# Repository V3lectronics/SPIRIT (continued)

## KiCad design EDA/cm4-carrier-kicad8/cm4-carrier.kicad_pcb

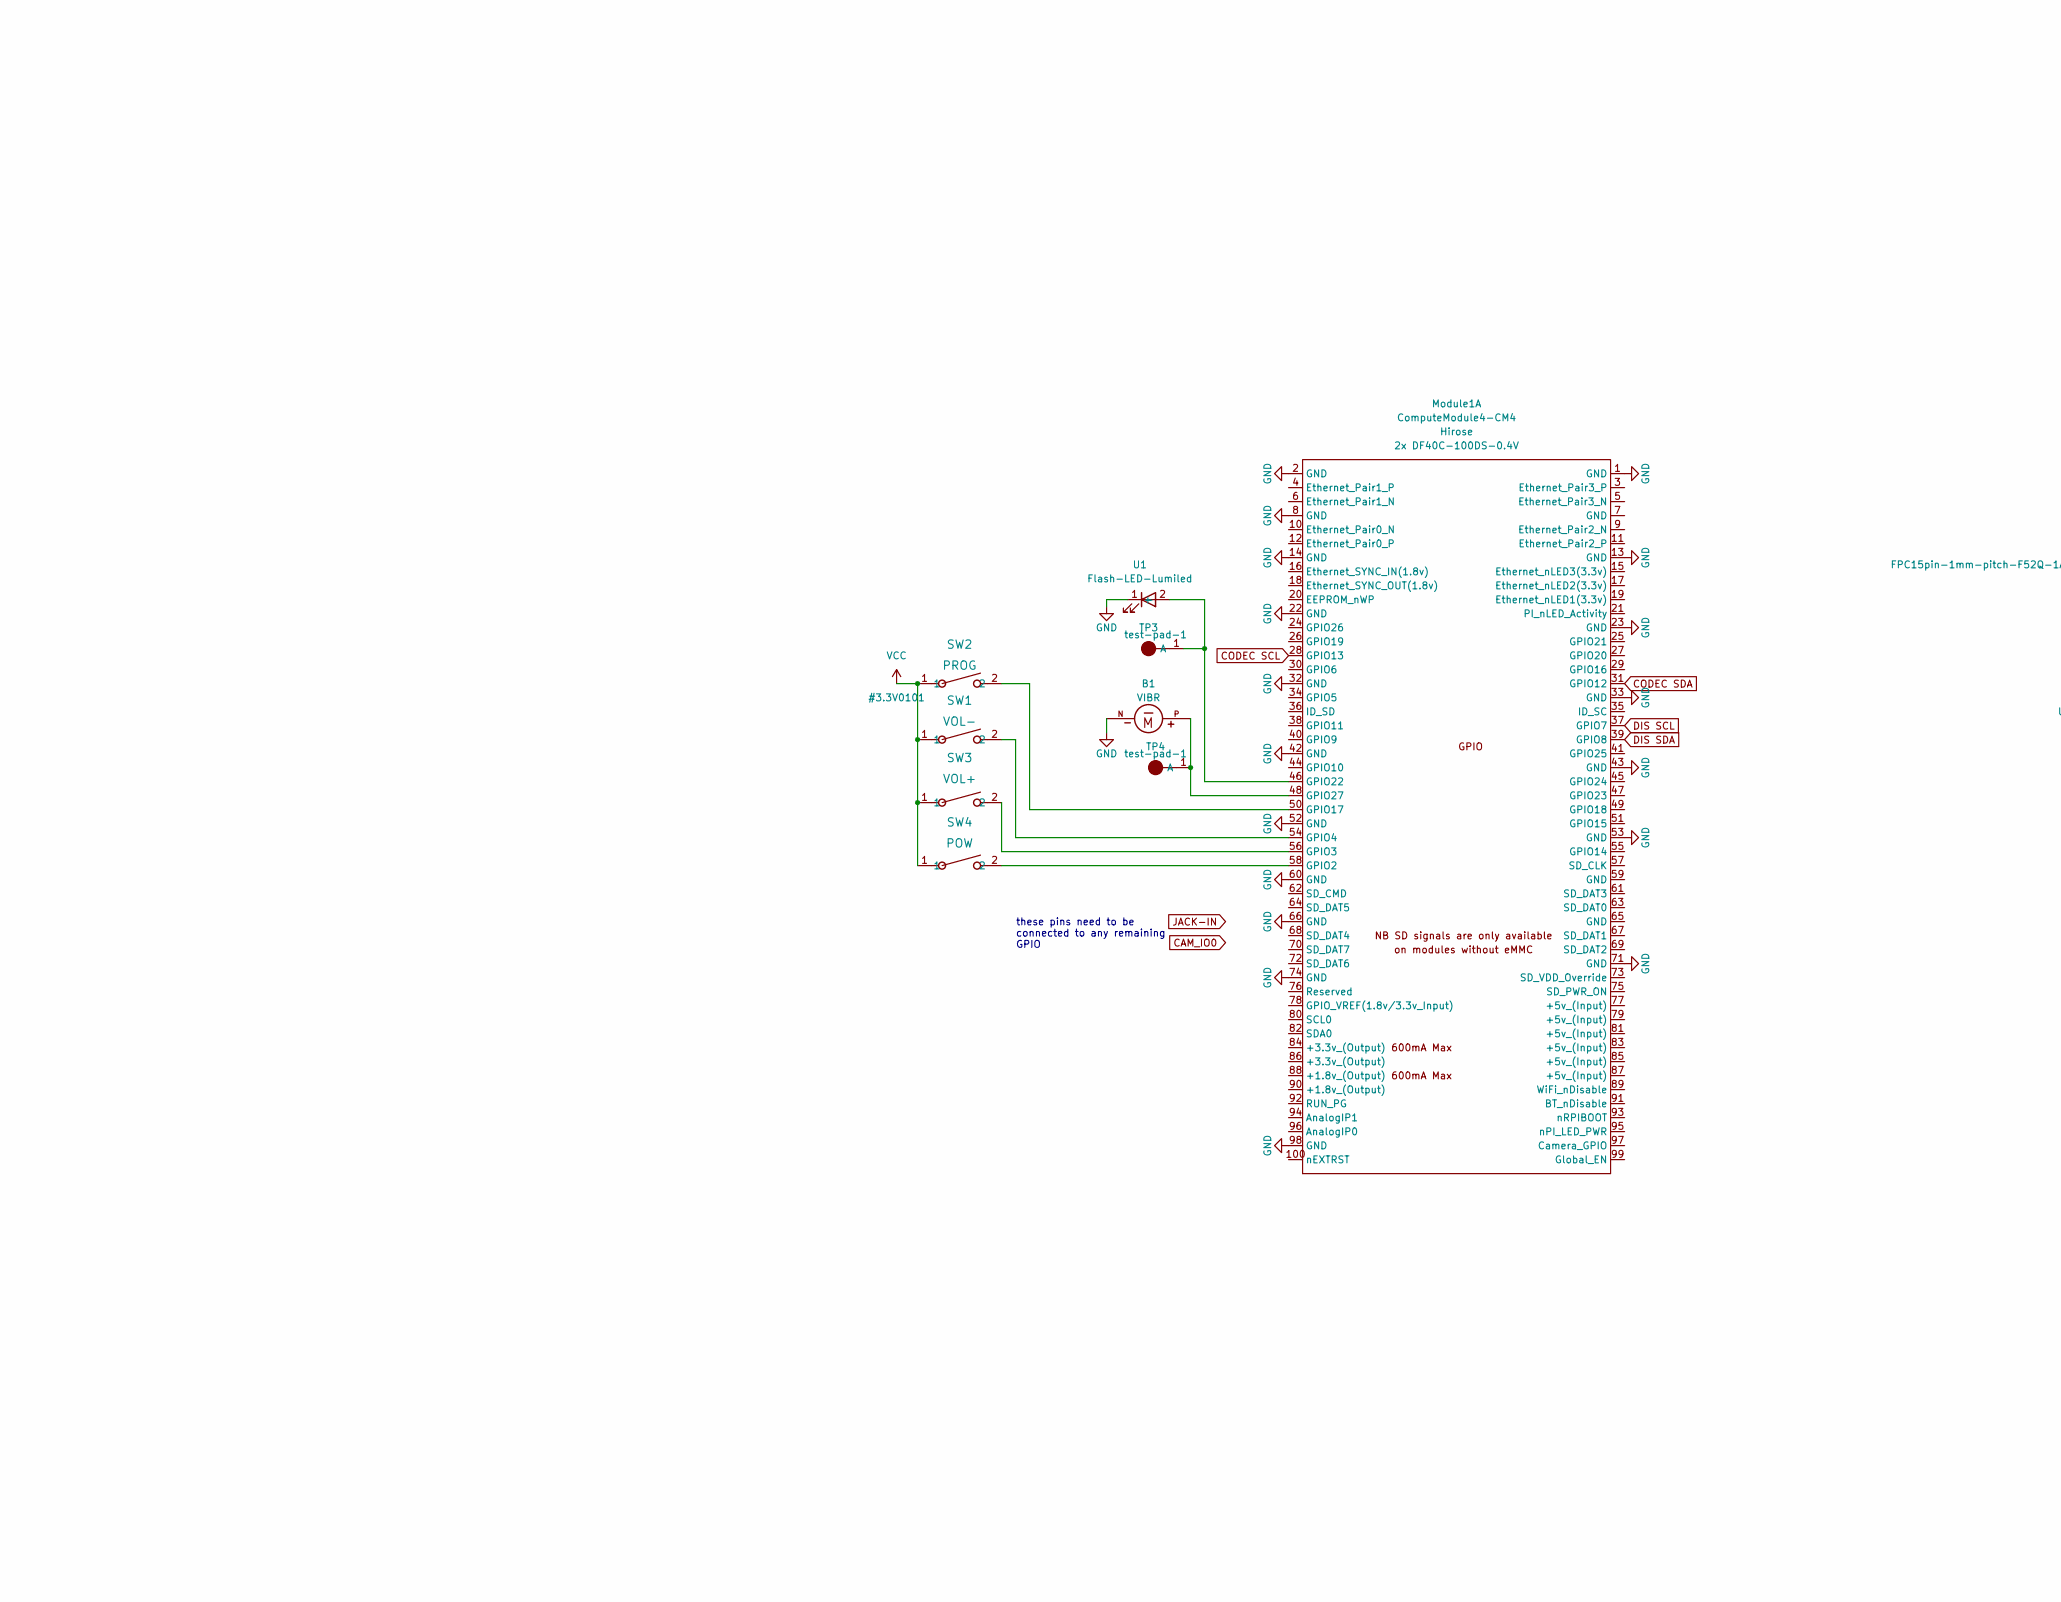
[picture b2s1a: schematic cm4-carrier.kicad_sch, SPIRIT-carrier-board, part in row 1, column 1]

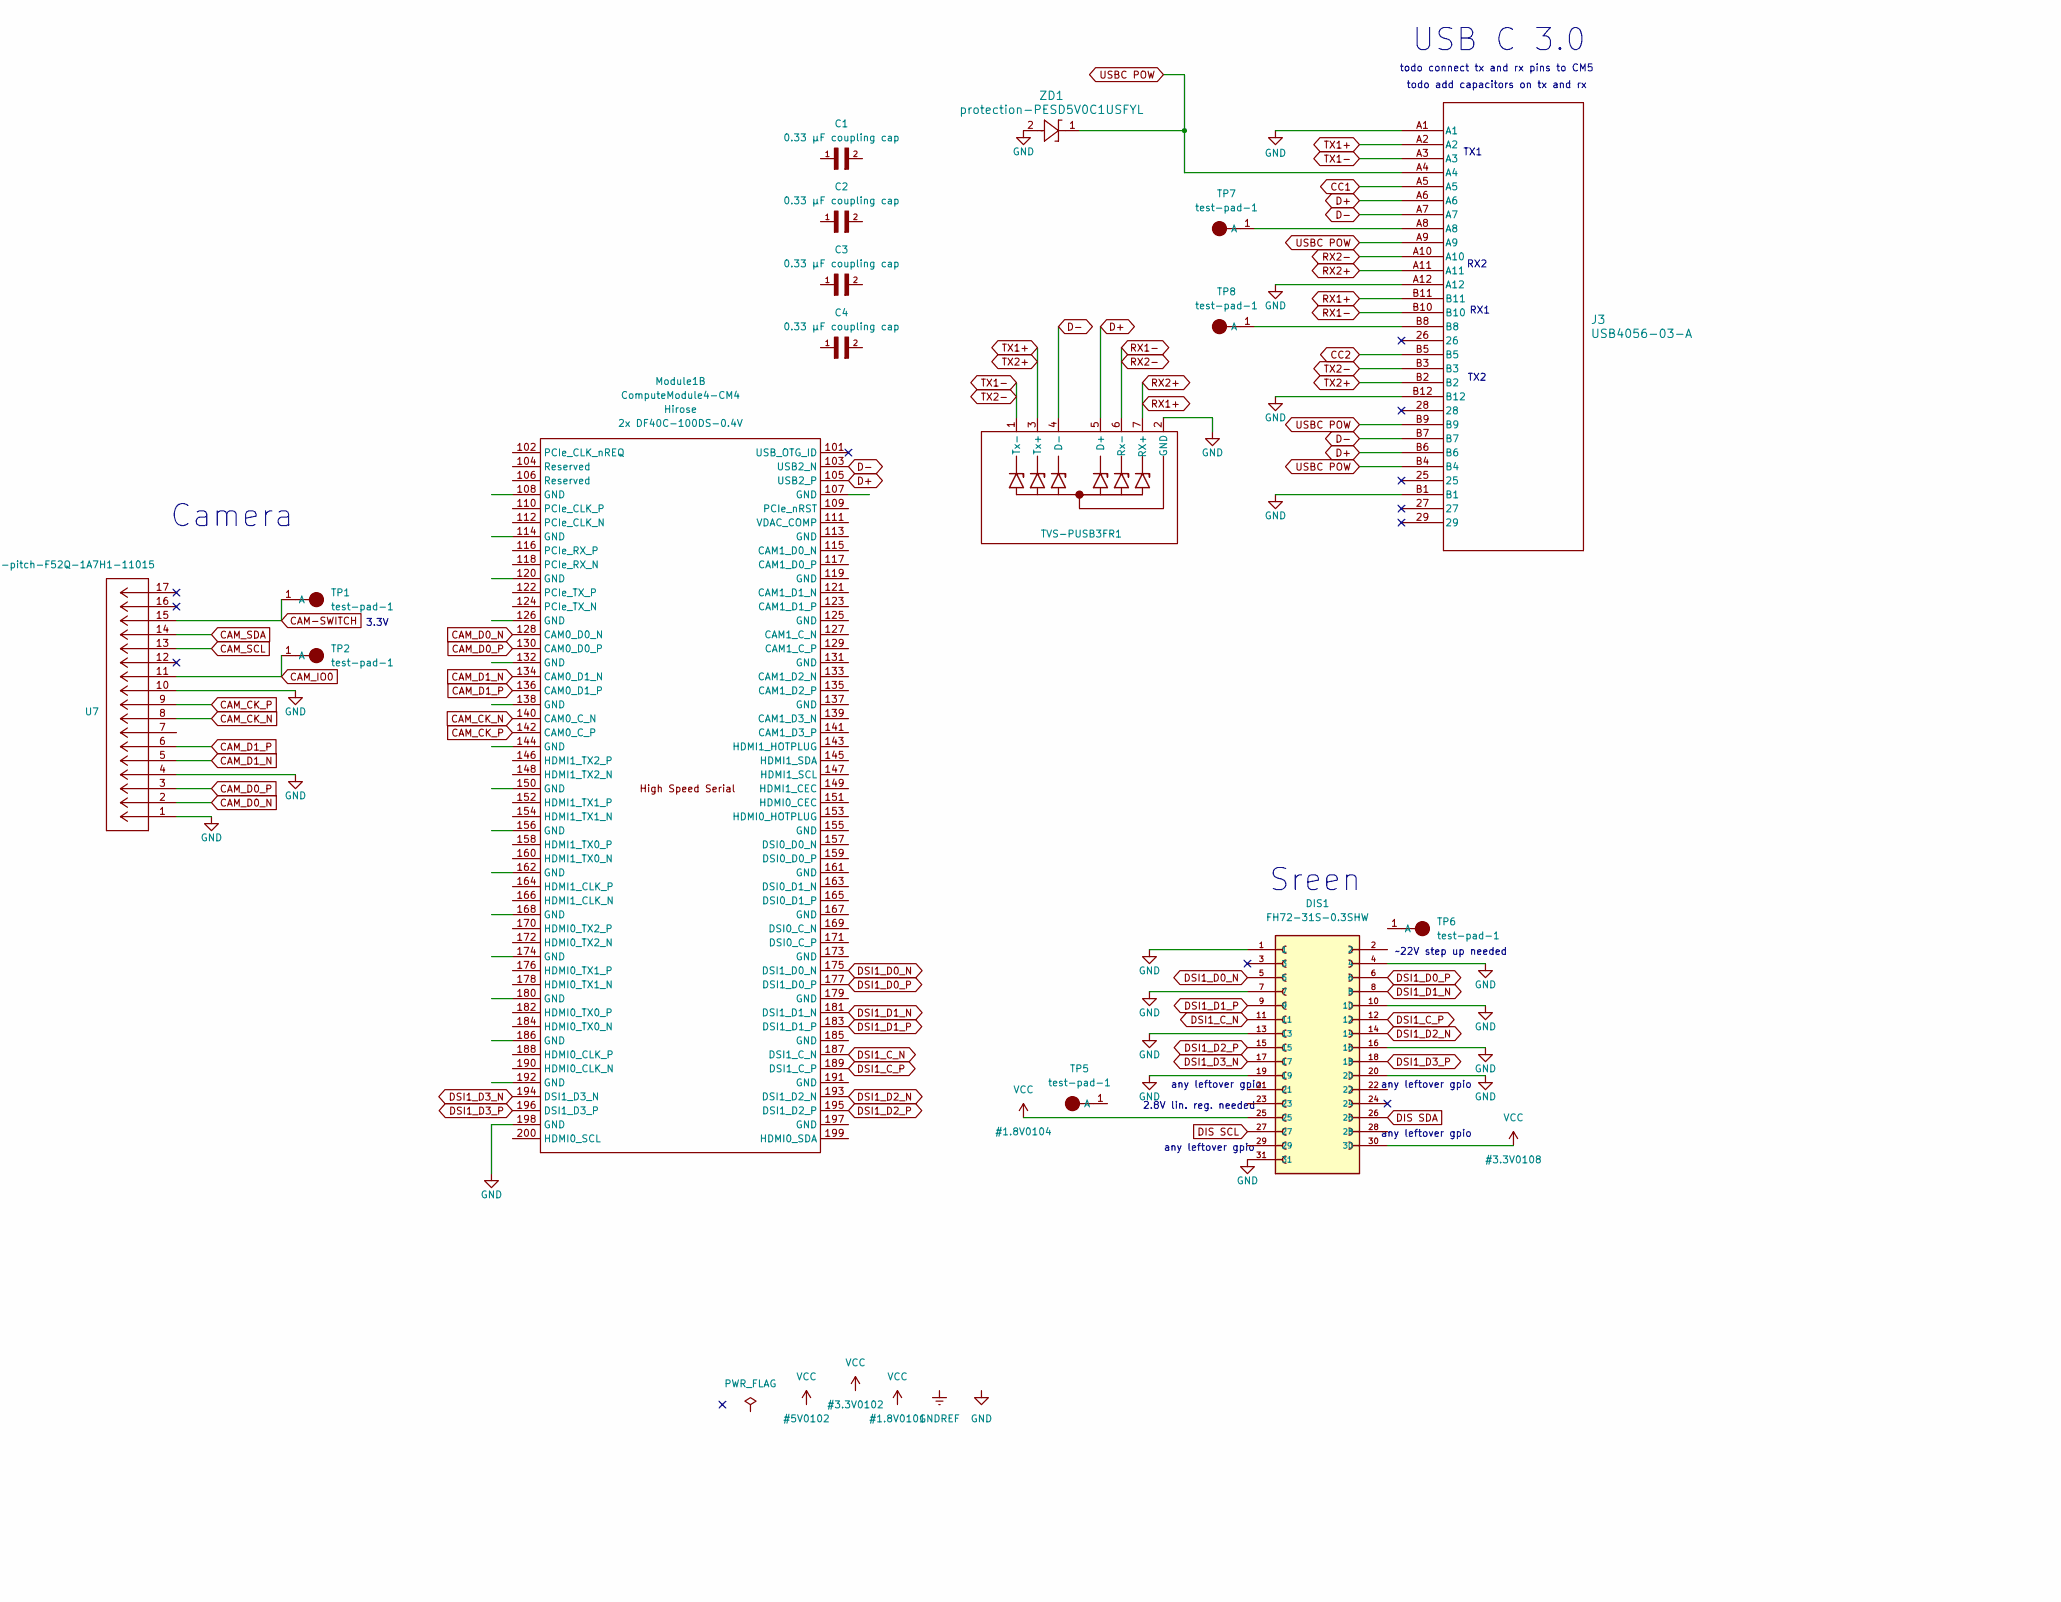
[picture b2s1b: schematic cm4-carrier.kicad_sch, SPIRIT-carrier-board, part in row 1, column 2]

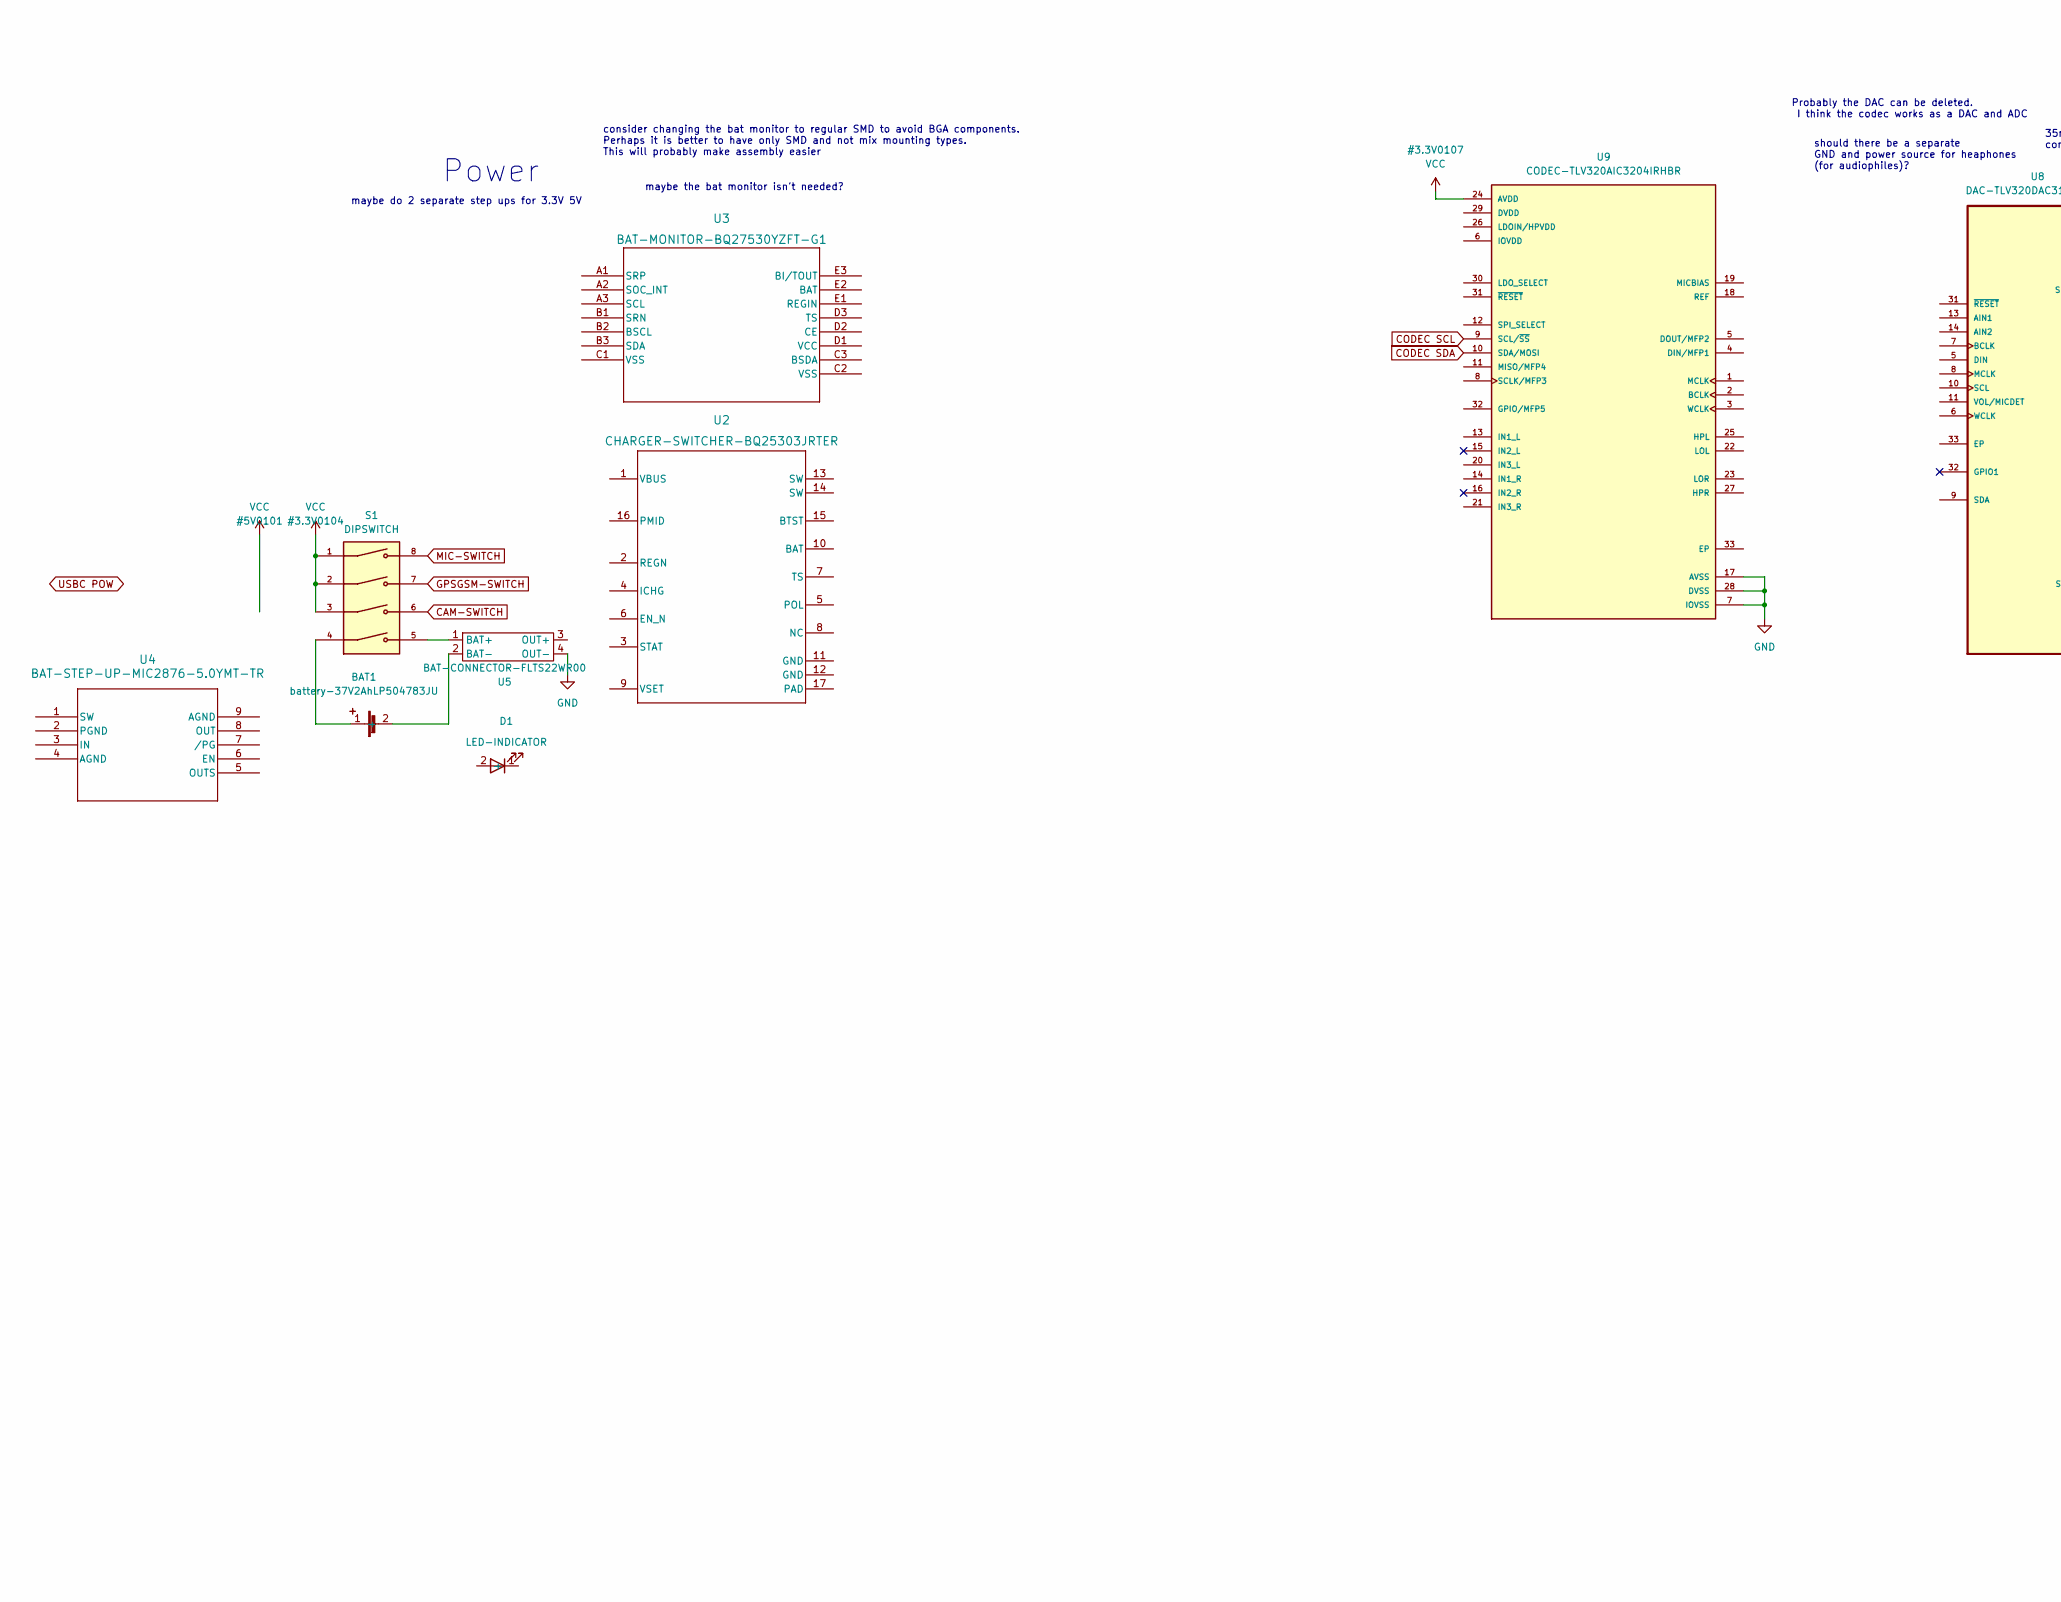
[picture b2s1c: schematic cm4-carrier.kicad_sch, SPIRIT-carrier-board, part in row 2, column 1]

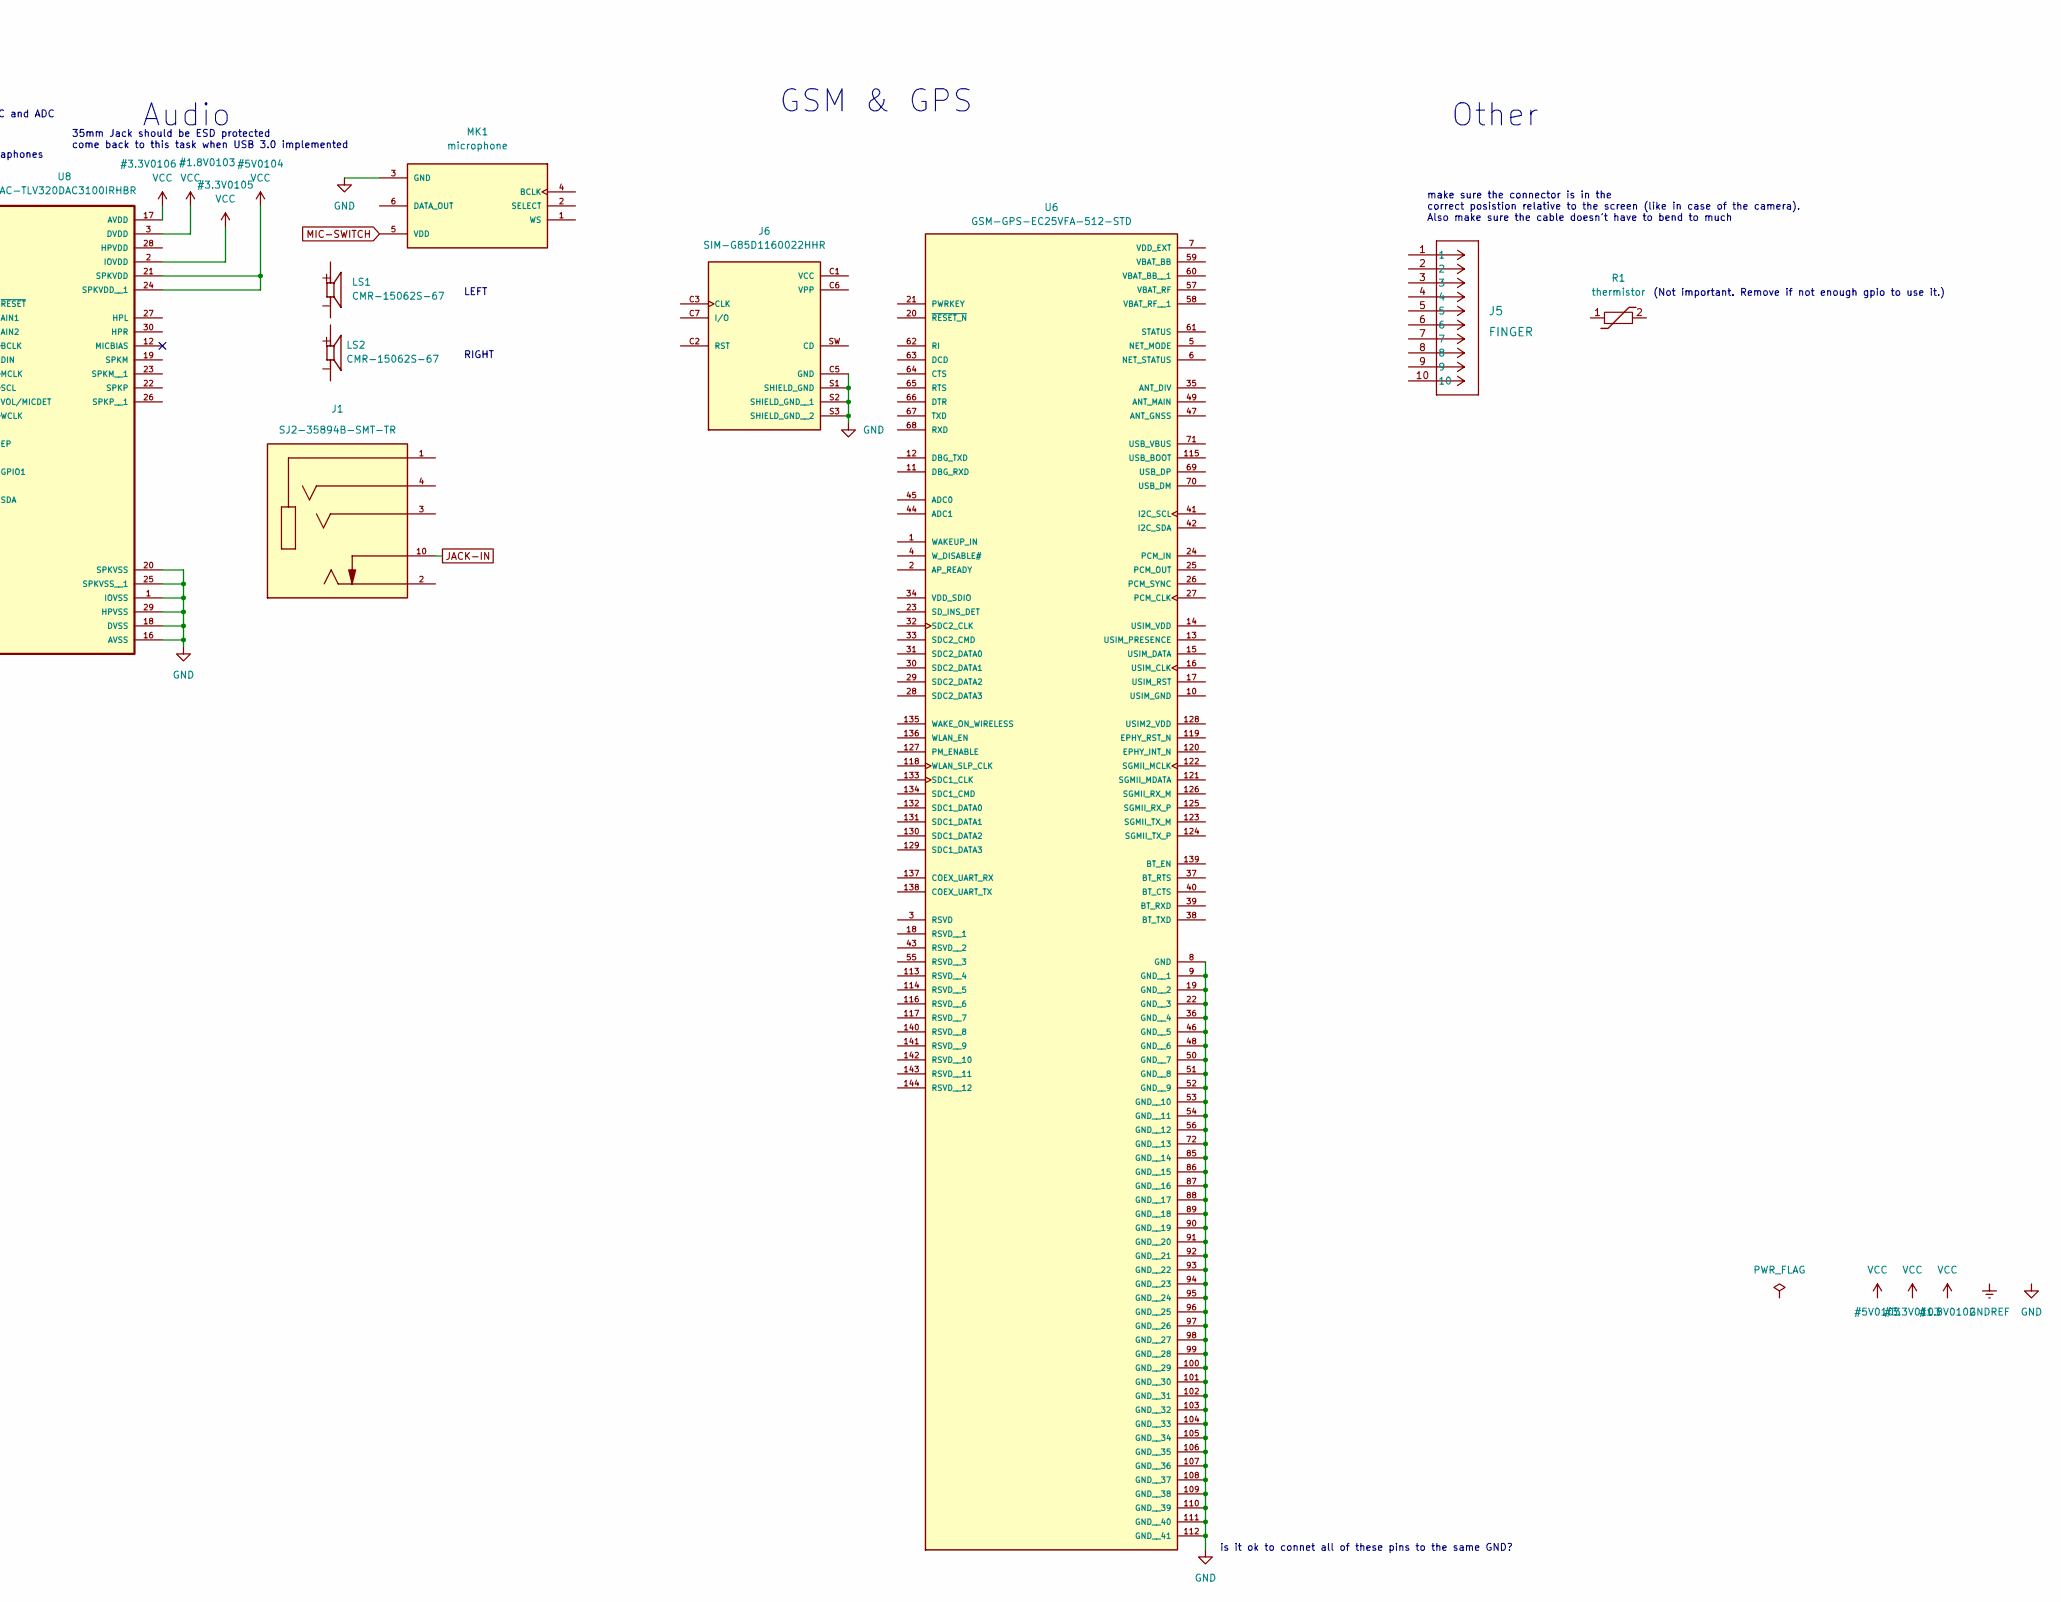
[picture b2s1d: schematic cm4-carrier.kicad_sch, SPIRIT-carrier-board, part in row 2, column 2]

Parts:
B1: VIBR; VIBRATION-PUI_HD-EMB1205-3-SC-R; PARTREV B
BAT1: battery-37V2AhLP504783JU
C1, C2, C3, C4: 0.33 µF coupling cap; USBC_capacitor_CAPC0603X33N
D1: LED-INDICATOR
DIS1: FH72-31S-0.3SHW; HRS_FH72-31S-0.3SHW; PARTREV 20201105
J1: SJ2-35894B-SMT-TR; 35mmJACK-CUI_SJ2-35894B-SMT-TR; PARTREV 1.04; DigiKey_Part_Number CP-SJ2-35894B-SMT-TR-ND
J3: USB4056-03-A; USBC3-2
J5: FINGER; 10PIN
J6: SIM-G85D1160022HHR; SIM-AMPHENOL_G85D1160022HHR; PARTREV AX3
LS1, LS2: CMR-15062S-67; SPEAKER_CMR-15062S-67; PARTREV 1.0
MK1: microphone; microphone_SPH0645LM4H-B
Module1: ComputeModule4-CM4; Raspberry-Pi-4-Compute-Module
R1: thermistor; thermistor-NTC0201Z_P63XP33_PAN
S1: DIPSWITCH; DIPSWITC-SW_219-4MST; PARTREV C
SW1: VOL-; buttonSW_TL3330_EWI
SW2: PROG; buttonSW_TL3330_EWI
SW3: VOL+; buttonSW_TL3330_EWI
SW4: POW; buttonSW_TL3330_EWI
TP1, TP2, TP3, TP4, TP5, TP6, TP7, TP8: test-pad-1
TVS-PUSB3FR1: TVS-array-IC_PUSB3AB6Z
U1: Flash-LED-Lumiled; LUMILED-DIODFN449X305X210-3N
U2: CHARGER-SWITCHER-BQ25303JRTER; CHARGER-SWITCHER-RTE0016C
U3: BAT-MONITOR-BQ27530YZFT-G1; BAT-MONITOR-YZF15_TEX
U4: BAT-STEP-UP-MIC2876-5.0YMT-TR; BAT-STEP-UP-UDFN8_2X2_MCH
U5: BAT-CONNECTOR-FLTS22WR00
U6: GSM-GPS-EC25VFA-512-STD; GSM-GPS-XCVR_EC25VFA-512-STD
U7: FPC15pin-1mm-pitch-F52Q-1A7H1-11015; FPC15pin-1mm-pitch-CONN_F52Q-1A7H1-11015_AMP
U8: DAC-TLV320DAC3100IRHBR; DAC-IC_ADS125H01IRHBT
U9: CODEC-TLV320AIC3204IRHBR; CODEC-QFN50P500X500X100-33N; PARTREV E
ZD1: protection-PESD5V0C1USFYL; USB-ESD-protection-diode-PESD5V0C1USFYL-SOD962-2_DSN0603-2_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

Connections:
CAM-SWITCH: S1.6, TP1.1 (A), U7.15
CAM_CK_N: Module1.140 (CAM0_C_N), U7.8
CAM_CK_P: Module1.142 (CAM0_C_P), U7.9
CAM_D0_N: Module1.128 (CAM0_D0_N), U7.2
CAM_D0_P: Module1.130 (CAM0_D0_P), U7.3
CAM_D1_N: Module1.134 (CAM0_D1_N), U7.5
CAM_D1_P: Module1.136 (CAM0_D1_P), U7.6
CAM_IO0: TP2.1 (A), U7.11
CAM_SCL: U7.13
CAM_SDA: U7.14
CC1: J3.A5
CC2: J3.B5
CODEC SCL: Module1.28 (GPIO13), U9.9 (SCL/~SS)
CODEC SDA: Module1.31 (GPIO12), U9.10 (SDA/MOSI)
D+: J3.A6, J3.B6, Module1.105 (USB2_P), TVS-PUSB3FR1.5 (D+)
D-: J3.A7, J3.B7, Module1.103 (USB2_N), TVS-PUSB3FR1.4 (D-)
DIS SCL: DIS1.27, Module1.37 (GPIO7)
DIS SDA: DIS1.26, Module1.39 (GPIO8)
DSI1_C_N: DIS1.11, Module1.187 (DSI1_C_N)
DSI1_C_P: DIS1.12, Module1.189 (DSI1_C_P)
DSI1_D0_N: DIS1.5, Module1.175 (DSI1_D0_N)
DSI1_D0_P: DIS1.6, Module1.177 (DSI1_D0_P)
DSI1_D1_N: DIS1.8, Module1.181 (DSI1_D1_N)
DSI1_D1_P: DIS1.9, Module1.183 (DSI1_D1_P)
DSI1_D2_N: DIS1.14, Module1.193 (DSI1_D2_N)
DSI1_D2_P: DIS1.15, Module1.195 (DSI1_D2_P)
DSI1_D3_N: DIS1.17, Module1.194 (DSI1_D3_N)
DSI1_D3_P: DIS1.18, Module1.196 (DSI1_D3_P)
GND: B1.N, DIS1.1, DIS1.4, DIS1.7, DIS1.10, DIS1.13, DIS1.16, DIS1.19, DIS1.20, DIS1.31, J3.A1, J3.A12, J3.B1, J3.B12, J6.C5 (GND), J6.S1 (SHIELD_GND), J6.S2 (SHIELD_GND__1), J6.S3 (SHIELD_GND__2), MK1.3 (GND), Module1.1 (GND), Module1.2 (GND), Module1.8 (GND), Module1.13 (GND), Module1.14 (GND), Module1.22 (GND), Module1.23 (GND), Module1.32 (GND), Module1.33 (GND), Module1.42 (GND), Module1.43 (GND), Module1.52 (GND), Module1.53 (GND), Module1.60 (GND), Module1.66 (GND), Module1.71 (GND), Module1.74 (GND), Module1.98 (GND), Module1.198 (GND), TVS-PUSB3FR1.2 (GND), U1.1 (-), U5.4 (OUT-), U6.8 (GND), U6.9 (GND__1), U6.19 (GND__2), U6.22 (GND__3), U6.36 (GND__4), U6.46 (GND__5), U6.48 (GND__6), U6.50 (GND__7), U6.51 (GND__8), U6.52 (GND__9), U6.53 (GND__10), U6.54 (GND__11), U6.56 (GND__12), U6.72 (GND__13), U6.85 (GND__14), U6.86 (GND__15), U6.87 (GND__16), U6.88 (GND__17), U6.89 (GND__18), U6.90 (GND__19), U6.91 (GND__20), U6.92 (GND__21), U6.93 (GND__22), U6.94 (GND__23), U6.95 (GND__24), U6.96 (GND__25), U6.97 (GND__26), U6.98 (GND__27), U6.99 (GND__28), U6.100 (GND__29), U6.101 (GND__30), U6.102 (GND__31), U6.103 (GND__32), U6.104 (GND__33), U6.105 (GND__34), U6.106 (GND__35), U6.107 (GND__36), U6.108 (GND__37), U6.109 (GND__38), U6.110 (GND__39), U6.111 (GND__40), U6.112 (GND__41), U7.1, U7.4, U7.10, U8.1 (IOVSS), U8.16 (AVSS), U8.18 (DVSS), U8.20 (SPKVSS), U8.25 (SPKVSS__1), U8.29 (HPVSS), U9.7 (IOVSS), U9.17 (AVSS), U9.28 (DVSS), ZD1.2; also elsewhere on the board
GPSGSM-SWITCH: S1.7
JACK-IN: J1.10
MIC-SWITCH: MK1.5 (VDD), S1.8
unnamed: BAT1.1 (+), S1.4
unnamed: BAT1.2 (-), U5.2 (BAT-)
unnamed: Module1.58 (GPIO2), SW4.2
unnamed: Module1.56 (GPIO3), SW3.2
unnamed: Module1.54 (GPIO4), SW1.2
unnamed: Module1.50 (GPIO17), SW2.2
unnamed: Module1.46 (GPIO22), TP3.1 (A), U1.2 (+)
unnamed: B1.P, Module1.48 (GPIO27), TP4.1 (A)
unnamed: J3.A8, TP7.1 (A)
unnamed: J3.B8, TP8.1 (A)
unnamed: S1.5, U5.1 (BAT+)
RX1+: J3.A11, J3.B11, TVS-PUSB3FR1.7 (RX+)
RX1-: J3.A10, J3.B10, TVS-PUSB3FR1.6 (Rx-)
TX1+: J3.A2, J3.B2, TVS-PUSB3FR1.3 (Tx+)
TX1-: J3.A3, J3.B3, TVS-PUSB3FR1.1 (Tx-)
USBC POW: J3.A4, J3.A9, J3.B4, J3.B9, ZD1.1
VCC: DIS1.25, DIS1.30, S1.1, S1.2, S1.3, SW1.1, SW2.1, SW3.1, SW4.1, U8.2 (IOVDD), U8.3 (DVDD), U8.17 (AVDD), U8.21 (SPKVDD), U8.24 (SPKVDD__1), U9.24 (AVDD)

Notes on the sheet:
make sure the connector is in the correct posistion relative to the screen (like in case of the camera). Also make sure the cable doesn't have to bend to much
maybe the bat monitor isn't needed?
TX1
Probably the DAC can be deleted. I think the codec works as a DAC and ADC
LEFT
should there be a separate GND and power source for heaphones (for audiophiles)?
35mm Jack should be ESD protected come back to this task when USB 3.0 implemented
Camera
todo connect tx and rx pins to CM5
todo add capacitors on tx and rx
maybe do 2 separate step ups for 3.3V 5V
Sreen
GSM & GPS
USB C 3.0
~22V step up needed
Audio
Power
TX2
any leftover gpio
RIGHT
RX2
Other
consider changing the bat monitor to regular SMD to avoid BGA components. Perhaps it is better to have only SMD and not mix mounting types. This will probably make assembly easier
RX1
is it ok to connet all of these pins to the same GND?
3.3V
(Not important. Remove if not enough gpio to use it.)
2.8V lin. reg. needed
these pins need to be connected to any remaining GPIO

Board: 2 copper layers, 44 parts (3 on the bottom side), 41 nets, no tracks yet.

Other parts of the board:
R2, R3: 5.1kOhm; CC-PULLDOWN-RESISOTR
logo1: KiCad-Logo2_5mm_SilkScreen

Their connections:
GND: R2.1, R3.2; also elsewhere on the board

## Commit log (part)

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2024-08-09 connectivity
2024-08-13 branding
2024-08-13 switch to cm4
2024-08-13 welcome contribution
2024-08-17 add architecture diagram
2024-08-30 add EDA software paragraph
2024-08-30 typo
2024-08-30 add table
2024-09-01 modify text
2024-09-01 add text
2024-09-02 remove mega pixels category
2024-09-02 add V Electronics logos
2024-09-05 remove problem section
2024-09-06 add parts and note to self
2024-09-09 add EDA files
2024-09-10 fix heading sizes
2024-09-10 add badge and contrib
2024-09-10 add contributing link
2024-09-10 Revert "add contributing link"
    This reverts commit 041ce198a2996b5441ceb1b91745f6dd39392926.
2024-09-12 add ve branding
2024-09-12 Update architecture
2024-09-13 add categories
2024-09-13 fix links
2024-09-13 add attributions
2024-09-13 update EDA files
2024-09-21 update files
2024-09-23 update images and architecture
2024-11-10 Update images and remove "architecture"
2024-12-01 switch to kicad 8
2024-12-01 add info about discord
2024-12-24 add contribution guide
2024-12-24 typo, formating
2024-12-24 typos
2024-12-24 wording
2024-12-24 pause invites
2024-12-24 add contrib guide link
2024-12-24 fix link
2024-12-24 fix contribution link
2024-12-24 add rule
2024-12-26 update docs
2024-12-28 update readme to cm5
2024-12-31 add link to tasks list
2024-12-31 add tasks list file
2024-12-31 change sections
2024-12-31 add stars and change formating
2025-01-05 finish USB C 32
2025-01-05 finish USB C kicad 8
2025-01-05 add CM5 symbols footrpints and models
2025-07-01 early renders
2025-07-01 add more filetypes
2025-07-01 remove old backups
2025-07-01 exclude env for helper script
2025-07-01 massive cleanup
2025-07-01 remove old files
2025-07-01 fix USB C EDA files & add usb c pinout to schematic
2025-07-01 remove not needed files
2025-07-01 remove old text
2025-07-01 improve text
2025-07-01 add logo
2025-07-01 add spacing
2025-07-01 add proper checkbox
2025-07-01 rearrange intro
2025-07-02 add cutout for battery
2025-07-03 increase cutout to 51.5 x 78.5
2025-07-03 New battery, its now a 3500mah one
2025-07-04 remove levitating bat leads
2025-07-15 flashlight and vibration MOSFET drivers
2025-07-17 Added the new power system. Some resistor values are still missing
2025-07-25 split schematic into multiple files
2025-07-25 Power system is finally working, i hope so atleast. Issues are the syme as gefore (2 resistors missing values and a missing BATFET connection, but everything is marked so it should be easy to find
2025-07-28 Added a freecad model for the body
2025-07-29 add caution message
2025-07-30 improve file structure
2025-07-30 update tasks
2025-07-30 update text
2025-07-31 Selected specific LED, fixed the wrong connections and connected the system to the usb
2025-08-09 fix'ed 3D models
2025-08-09 fixed paths
    there where a bit wrong last time
2025-08-09 more paths fixed
2025-08-09 thermistor fixed
2025-08-09 cm module fixed
2025-08-10 added brick models for battery and fingerprint scanner
2025-08-10 last button now flush with board edge
2025-08-10 moved off board components near what they control
2025-08-10 added 3d model for flashlight
2025-08-10 finger print scanner model added
    we still need to board connector
2025-08-10 enabled the top speaker
    forgot that i had set it to hidden
2025-08-10 better (i think) cm5 model
2025-08-10 finger print scanner connected
    missing pin 6 and 7, and we still need a 3d model of the connector for the board
    link to datasheet: https://mm.digikey.com/Volume0/opasdata/d220001/medias/docus/5676/SPC26627-3_BM-LITE_Safetouch_Spec.pdf
2025-08-11 remove task list, see issues
2025-08-11 link to issues instead of task list
2025-08-11 edit text
2025-08-11 docs: improved layout of readme
    improved layout of readme.
2025-08-11 docs: compressed images in the branding folder
2025-08-12 fixed audio jack and usb placement
2025-08-12 #10 Added Battery 3D Model (STEP)
2025-08-12 schematic cleaned up a bit
2025-08-12 update and improve layout
2025-08-12 Applied your fixes
2025-08-13 fix's as per discord caht
2025-08-13 and here is fingerprint sch
2025-08-13 link new battery model to footprint
2025-08-13 fully sync pcb to schematic, fix some models
2025-08-13 add fingerprint scanner FPC connector model
2025-08-13 remove SBU test pads from USB C
2025-08-14 3d model of figner scanner re-enabled
    someone (prob me) turned it off and did not enable it again
2025-08-14 TVS and ZD2
2025-08-14 added footprints to transistors
    used the footprint assigned to Q1
    check my work
2025-08-14 added footprint for diodes
    and also added the pcb update report
2025-08-14 updated the pcb
    we still have errors and we need to check the correct footprints are selected for each component
2025-08-14 Revert "updated the pcb"
    This reverts commit b83bfcf242b39ab1cc39cb22d321c5bb6567aa93.
2025-08-14 update pcb
    trying again
2025-08-14 remove report
2025-08-14 center USBC, mount speakers simmmetricallly
2025-08-14 remove CM5 drill hole avoiding EC25 conflict
2025-08-14 fix power button clearance issue
2025-08-14 add symmetry lines to layout
2025-08-14 added step files for the touchscreen (RK055AHD091-CTG)
2025-08-14 adjusted colors
2025-08-14 fix camera mount point
2025-08-14 finish fingerprint sensor placement
2025-08-14 add cutout for fingerprint sensor cable
2025-08-14 Add postmarketos as a potential OS
2025-08-15 add corner drill holes
2025-08-15 add screen model
2025-08-15 add branding
2025-08-15 add screenshots
2025-08-15 Update README.md
    updated images section
2025-08-15 Update README.md
    double tables images
2025-08-15 Update README.md ALL info moved to wiki
2025-08-16 logo notice
2025-08-16 Update and rename LICENSE to LICENSE.md
    update license info
2025-08-16 Update LICENSE.md
    improve text
2025-08-16 add licenses
2025-08-16 Update README.md
    move trademark notice
2025-08-16 Update LICENSE.md
    add trademark info
2025-08-17 M.2 nvme connector added. I know you didnt whant it now but i was bored
2025-08-19 change file extensions so they maybe appear on gh?
2025-08-19 Revert "change file extensions so they maybe appear on gh?"
    This reverts commit 1b93e96c5384c0912f3eae2b4a175f1415d872c9.
2025-08-20 add dirs for future addons
2025-08-20 add EG25 new gpsgsm
2025-08-20 new component layout to fix cm5 heat issue
2025-08-21 fix hole sizes
2025-08-21 upgrade usb c to waterproof and 4-0
2025-08-22 added button cutouts
2025-08-22 fix buttons 2
2025-08-23 add clearance
2025-08-25 microhphone partially connected
2025-08-27 Did everything you whanted me to do
2025-08-27 Stop tracking EDA-kicad/Storage.kicad_sch
2025-09-01 Completely wired up power section. Ill do the cm5 5v rail in a latercommit, just so this commit isnt growing too large. I put lots of work and thought in making it easy to work with, so i hope you li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
2025-09-02 complete microphone schematic
2025-09-02 Added the usb pow back and added the 5v @ 5a rail
2025-09-04 fix STAT pin LED, connect USB POW, remove d3
2025-09-05 add BSC0902NSI power section transistor
2025-09-08 connect charger IC pins 1 though 15
2025-09-08 connect charger IC pins 1 though 20
2025-09-09 exclude old EC25 and minor changes to power
2025-09-09 charger IC fully connected
2025-09-09 power improvements
2025-09-11 add charger IC label
2025-09-11 add fields to some symbols
2025-09-11 add example BOM from power schematic
2025-09-11 modify point 9
2025-09-11 add fields
2025-09-11 changes from last 3 commits
2025-09-12 add step, footprint and better symbol for 5V 5A rail
2025-09-12 MP3429 progress
2025-09-12 5V rail schematic complete
2025-09-16 moved fingerprint sensor approx 5mm down
2025-09-16 add 0805 cap
2025-09-16 implement 22V rail
2025-09-17 add notch for easier assembly
2025-09-17 example BOM
2025-09-17 added 22V regulator
2025-09-17 rename
2025-09-17 minor changes
2025-09-17 add note (test commit)
2025-09-18 add TPS650250 PMIC files
2025-09-18 connect L and VIN pins
2025-09-18 import symbol TPS650250
2025-09-18 TPS650250 3V3 and 1V8 rails connected, PWRFAIL threshold set
2025-09-18 modify TPS650 symbol
2025-09-18 organize power related signals
2025-09-18 set 6 layers, modify their settings
2025-09-19 Add roadmap to README.md
2025-09-20 swap mermaid graph to normal md text
2025-09-22 add charger thermistor
2025-09-22 add new 22V rail AP3032
2025-09-22 remove old TPS650 circuit
2025-09-22 add ap3032
2025-09-22 separate regulator EN labels for fine grained power saving features etc
2025-09-22 add 47k pwrfail pullup
2025-09-22 add placeholder symbols to 22V rail zener and r3
2025-09-22 reannotate entire schematic
2025-09-23 add schottky to 22V rail
2025-09-23 add monkeys
2025-09-23 finish 22V rail
2025-09-24 add new switches and reannotate
2025-09-25 add 2.2 inductor
2025-09-28 improve inductor symbol
2025-09-28 reannotate
2025-09-28 fix import schematic to pcb errors
2025-09-30 add schematic pdf
2025-09-30 improve and fix footprints, add mini silkscreen symbols
2025-09-30 more smd footprints improvements
2025-09-30 assign power section footprints and import to pcb
2025-09-30 add python automation script to set DNP
2025-09-30 set everything except from power to DNP
2025-10-02 add correct charger footprint and step file
2025-10-02 setup layers
2025-10-07 minor pcb progress
2025-10-12 add victoria fish pcb art
2025-11-30 FIxed PCB length as per TheTicraft (MavLeague) request
2026-01-03 fix: include any missing files
2026-01-05 Reduced the GPIO usage for the Buttons and redone the LED
2026-01-24 removed symbol and footprint for TPS650250 and replaced that PMIC TPS65023
2026-01-24 Removed TPS650250 symbol that was accidentally left behind
2026-01-24 Tidied the TPS65023 section up
2026-01-29 Fixed PCB outline and removed duplicate library "MP3429"
2026-02-06 remove old symbol library
2026-02-06 fix some symbols being imported separately from main library
2026-02-06 add information about "good first issue" label
2026-02-08 add battery fuse 1210L900SLPR
2026-02-08 add battery fuse to schematic
2026-02-09 fix fuse placement
2026-02-09 Added 1210-1812 universal size footprint for resettable fuse.
2026-02-10 add power calculations Octave file, double checked inductors, divider
2026-02-10 connect CM5 to 5V 6A rail
2026-02-10 connect VBACKUP to GND since no backup battery
2026-02-10 improve test pad symbol
2026-02-10 add test pad to VRTC
2026-02-10 distinguish between BQ INT and TPS INT pins
2026-02-10 Revert "Merge branch 'main' of https://github.com/Engineer162/SPIRIT"
    This reverts commit 4b9d5e5eeadd9fbbdfcd67c9cf1a6d4bc6ec3008, reversing
    changes made to 5bc2bb510634a0db9cf47dc57074958cd1daf157.
2026-02-10 Reapply "Merge branch 'main' of https://github.com/Engineer162/SPIRIT"
    This reverts commit faadb4b06c766ed7acf40c481909d61e62fd8808.
2026-02-10 Fixed Git having a meltdown
    Please send help git nuked my fork and i painfully reverted the stuff that got blown up. Also a 3D model's name made git go crazy so that was changed as well (the 3D model was UBAF30-D2011´+ê3D´+ë.ST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
2026-02-10 Fixed 3D model files having non ASCII file name characters and spaces
2026-02-10 If this file is still in the index im gonna crash out.
2026-02-19 disconnect RESPRWON_N for now
2026-02-25 swap VRTC cap
2026-02-25 add 10R to VCC (RC filter)
2026-02-25 PWRFAIL_SNS and LOWBAT_SNS dividers
2026-02-25 remove old notes
2026-02-27 applied no backup bat config to VSYSIN, removed standby label
2026-02-27 add testpad to INT
2026-03-03 remove snubbers, leave note, improve clarity
2026-03-03 fix wrong capacitors on DCDC output
2026-03-03 Add MPN to 0 Ohm jumper symbols, shorten text
2026-03-03 connect PMIC I2C to CM5
2026-03-05 update PCB layer descriptions
2026-03-07 Updated values of passive components
    Updated values of passive components (resistors and capacitors) to include Ohm symbol, and removed microfarads symbol replaced by "uf" to fix BOM generator confusion.
2026-03-13 apply standard PCBWay board stackup
2026-03-13 calculate min trace thickness of main pwr line
